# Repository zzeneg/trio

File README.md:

# trio

Modular unibody keyboard with two VIK modules.

> [!CAUTION]
> This keyboard is designed for minimal vertical spacing (19x16mm). Regular keycaps will not fit, you must print your own - for example my [DES MinY](https://github.com/zzeneg/PseudoMakeMeKeyCapProfiles?tab=readme-ov-file#update-from-zzeneg).
>
> It's created as a cheap prototype to test VIK abilities and modules - all PCBs are under 100x100mm, one-piece case <0.3kg for cheap JLCPCB shipping.
>
> Build process requires a lot of hand-soldering with 0.5mm pitch, you need good tools and experience to do that.
>
> I do not recommend to build it exactly like that, but to use it as inspiration for your projects. Feel free to use and improve KiCad and Fusion 360 source files.

## Features

- **MinY (19x16mm) spacing**
- 36 KS-33 (Gateron Low Profile) keys with hotswap
- central PCB with two independent VIKs, DRV2605L haptic feedback and rotary encoder
- periferal PCBs for keys
- 3D printed case with 1.28" display, Azoteq TPS65 touchpad and 33mm encoder

## Photos

## Gerber files

- [Main PCB](./pcb/production/main.zip)
- [Side PCB](./pcb/production/side.zip)
- Azoteq [VIK adapter](https://github.com/sadekbaroudi/vik/tree/master/pcb/azoteq-tps)
- Display [VIK adapter](https://github.com/zzeneg/vik-display-adapter) - 1.28" round version

## Case files

- [v0.1](./case/main-0.1.stl)
- [v0.2](./case/main-0.1.stl) - higher version, should work but untested

## Firmware

[Companion app](https://github.com/zzeneg/qmk-hid-host) for Raw HID communication. Use `"productId": 2120` for that keyboard.

#### QMK

Please see main `config.h` and `rules.mk` for comments and available options.

- [source code](https://github.com/zzeneg/qmk_firmware/tree/feature/zzeneg/keyboards/trio)
- [pre-compiled files](https://github.com/zzeneg/qmk_firmware/releases/tag/zzeneg)

#### Vial

- [source code](https://github.com/zzeneg/vial-qmk/tree/feature/zzeneg/keyboards/trio)
- [pre-compiled files](https://github.com/zzeneg/vial-qmk/releases/tag/zzeneg)

## Bill of materials

- [PCB](./pcb/production/pcb.zip)
- 36 KS-33 switches
- 36 hotswap sockets for KS-33 switches
- 3D printed case
- Azoteq TPS65 touchpad
- Azoteq [VIK adapter](https://github.com/sadekbaroudi/vik/tree/master/pcb/azoteq-tps)
- Bare 1.28" round [display](https://www.aliexpress.com/item/1005006051175539.html) - **without PCB**
- Display [VIK adapter](https://github.com/zzeneg/vik-display-adapter) - 1.28" round version **+ adapter's BOM**
- Helios-sized (26 GPIOs) [RP2040](https://www.aliexpress.com/item/1005006130019224.html) MCU
- 37 [SMD SOD-123 1N4148](https://www.aliexpress.com/item/1005002882901030.html) diodes
- [Vertical](https://www.aliexpress.com/item/10000000737049.html) and [horizontal](https://www.aliexpress.com/item/4000106123266.html) 12pin FFC/FPC connectors
- 12pin 0.5mm pitch 6cm [FFC cable](https://www.aliexpress.com/item/1005002468369055.html) - **both reverse and forward variants**
- short [EC11 rotary encoder](https://www.aliexpress.com/item/1005002109267228.html)
- 32mm [encoder knob](https://www.aliexpress.com/item/32749414806.html)
- SMD 4x4x1.5mm [push button](https://www.aliexpress.com/item/32802382507.html)
- 4mm [M2 screws with flat head](https://www.aliexpress.com/item/4001248931159.html)
- M2 [heatset inserts](https://www.aliexpress.com/item/1005004624377733.html) - 3mm length, 3.2mm diameter for resin case or 3.5mm for Nylon/PLA
- [7x1.5 legs](https://www.aliexpress.com/item/1005002995402961.html)
- for haptic feedback:
  - DRV2605L motor controller
  - 2 1uF capacitors (SMD 1206 size)
  - 2 4.7kOhm resistors (SMD 1206 size)
  - LRA or ERM [motor](https://docs.qmk.fm/#/feature_haptic_feedback?id=known-supported-hardware)

## Build notes

- side PCBs have two keys that have to be broken off and handwired to correct places (diodes stay on the big part)
- rotary encoder uses GPIO from VIK2, so Azoteq has to be connected to VIK2 port, and display to VIK1. Make sure to bridge solder jumpers on the back.
- cheap ERM motors may not have enough internal resistance, if you motor does not work, try to add 5-10R resistor to it
- see photos for FFC connections

## Development

For proper KiCad setup install my [zzkeeb](https://github.com/zzeneg/zzkeeb/blob/main/README.md#installation) library

## Support

If you like my work and want to support my future designs, please consider [sponsorship](https://github.com/sponsors/zzeneg).

#### Sponsors

Thank you very much for your support!

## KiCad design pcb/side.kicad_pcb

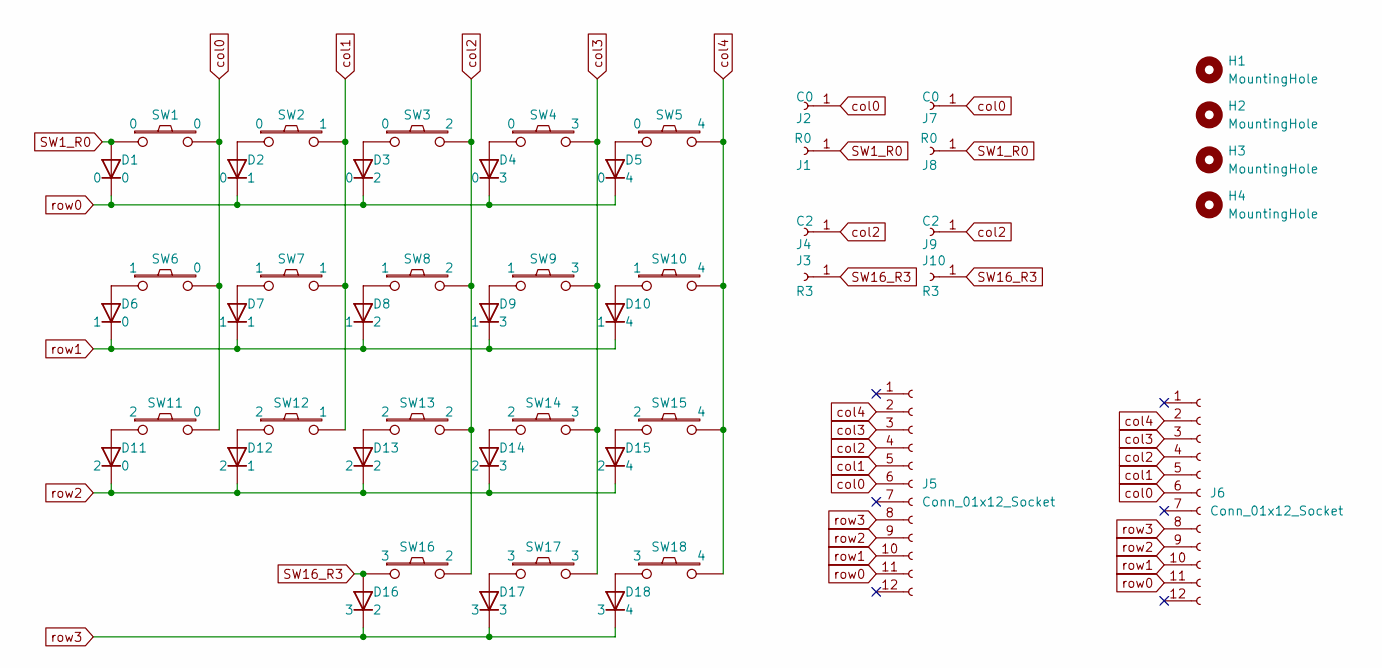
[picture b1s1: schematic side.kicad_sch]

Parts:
D1, D2, D3, D4, D5, D6, D7, D8, D9, D10, D11, D12, D13, D14, D15, D16, D17, D18: D; Diode_1N4148-SOD123-reversible-flip3d
H1, H2, H3, H4: MountingHole; Hole_M2
J1, J8: R0; TestPoint_THTPad_D1.5mm_Drill0.7mm
J2, J7: C0; TestPoint_THTPad_D1.5mm_Drill0.7mm
J3, J10: R3; TestPoint_THTPad_D1.5mm_Drill0.7mm
J4, J9: C2; TestPoint_THTPad_D1.5mm_Drill0.7mm
J5, J6: Conn_01x12_Socket; Connector_FFC-12pin-0.5mm-horizontal
SW1, SW2, SW3, SW4, SW5, SW6, SW7, SW8, SW9, SW10, SW11, SW12, SW13, SW14, SW15, SW16, SW17, SW18: Switch; Switch_KS-miny-reversible-hotswap-south

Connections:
unnamed: D2.2 (A), SW2.1
unnamed: D3.2 (A), SW3.1
unnamed: D4.2 (A), SW4.1
unnamed: D5.2 (A), SW5.1
unnamed: D6.2 (A), SW6.1
unnamed: D7.2 (A), SW7.1
unnamed: D8.2 (A), SW8.1
unnamed: D9.2 (A), SW9.1
unnamed: D10.2 (A), SW10.1
unnamed: D11.2 (A), SW11.1
unnamed: D12.2 (A), SW12.1
unnamed: D13.2 (A), SW13.1
unnamed: D14.2 (A), SW14.1
unnamed: D15.2 (A), SW15.1
unnamed: D17.2 (A), SW17.1
unnamed: D18.2 (A), SW18.1
SW1_R0: D1.2 (A), J1.1, J8.1, SW1.1
SW16_R3: D16.2 (A), J3.1, J10.1, SW16.1
col0: J2.1, J5.6, J6.6, J7.1, SW1.2, SW6.2, SW11.2
col1: J5.5, J6.5, SW2.2, SW7.2, SW12.2
col2: J4.1, J5.4, J6.4, J9.1, SW3.2, SW8.2, SW13.2, SW16.2
col3: J5.3, J6.3, SW4.2, SW9.2, SW14.2, SW17.2
col4: J5.2, J6.2, SW5.2, SW10.2, SW15.2, SW18.2
row0: D1.1 (K), D2.1 (K), D3.1 (K), D4.1 (K), D5.1 (K), J5.11, J6.11
row1: D6.1 (K), D7.1 (K), D8.1 (K), D9.1 (K), D10.1 (K), J5.10, J6.10
row2: D11.1 (K), D12.1 (K), D13.1 (K), D14.1 (K), D15.1 (K), J5.9, J6.9
row3: D16.1 (K), D17.1 (K), D18.1 (K), J5.8, J6.8

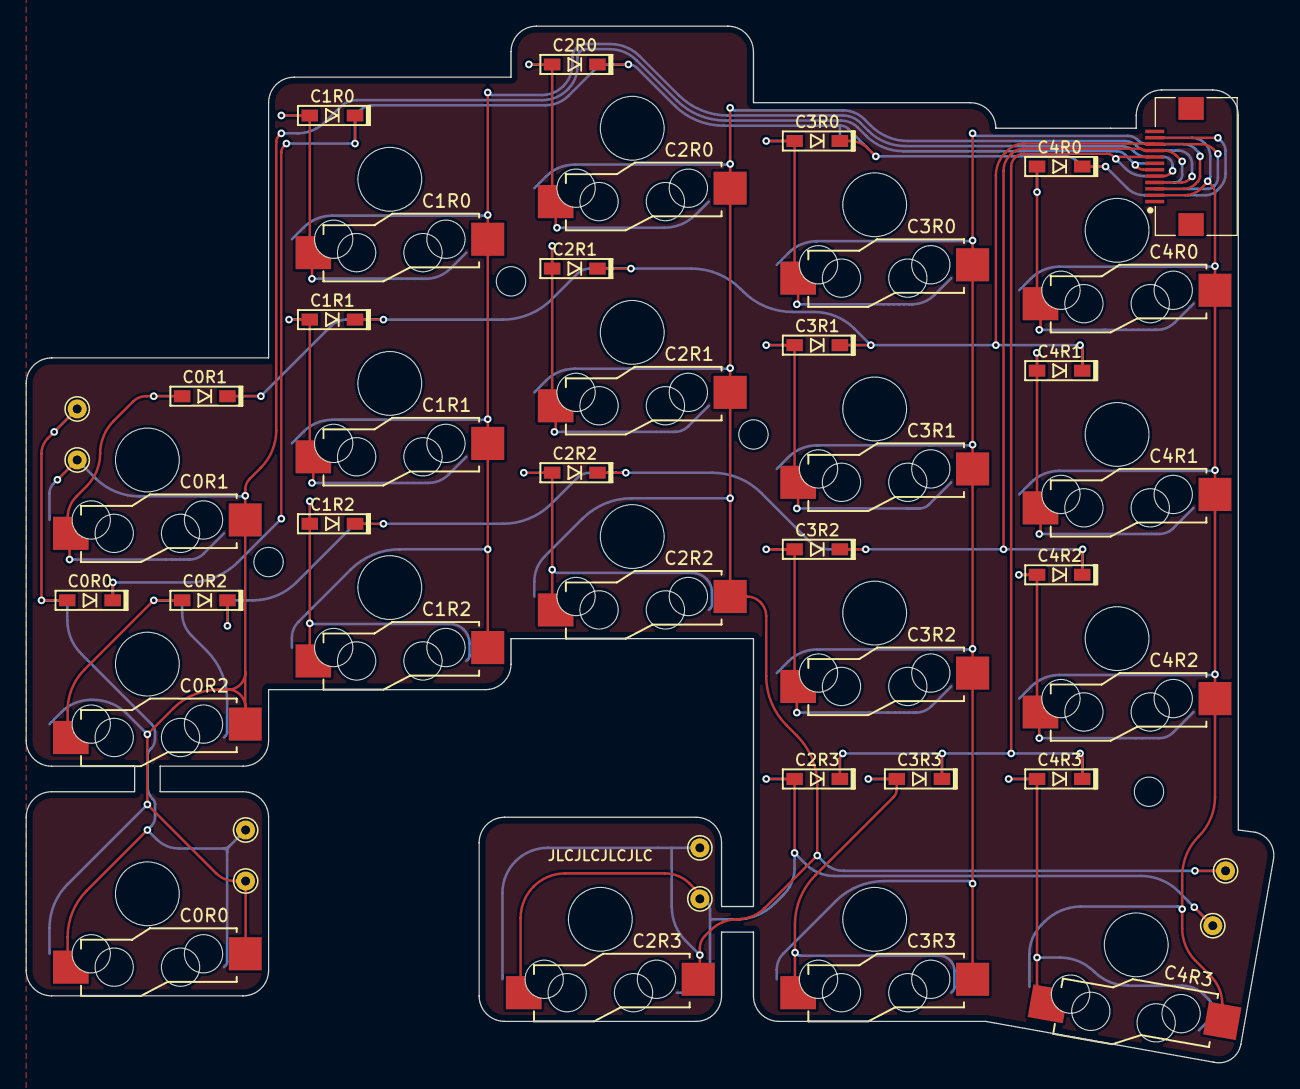
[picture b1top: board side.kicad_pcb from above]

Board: 2 copper layers, 97.8 x 81.2 mm, 50 parts (1 on the bottom side), 27 nets.

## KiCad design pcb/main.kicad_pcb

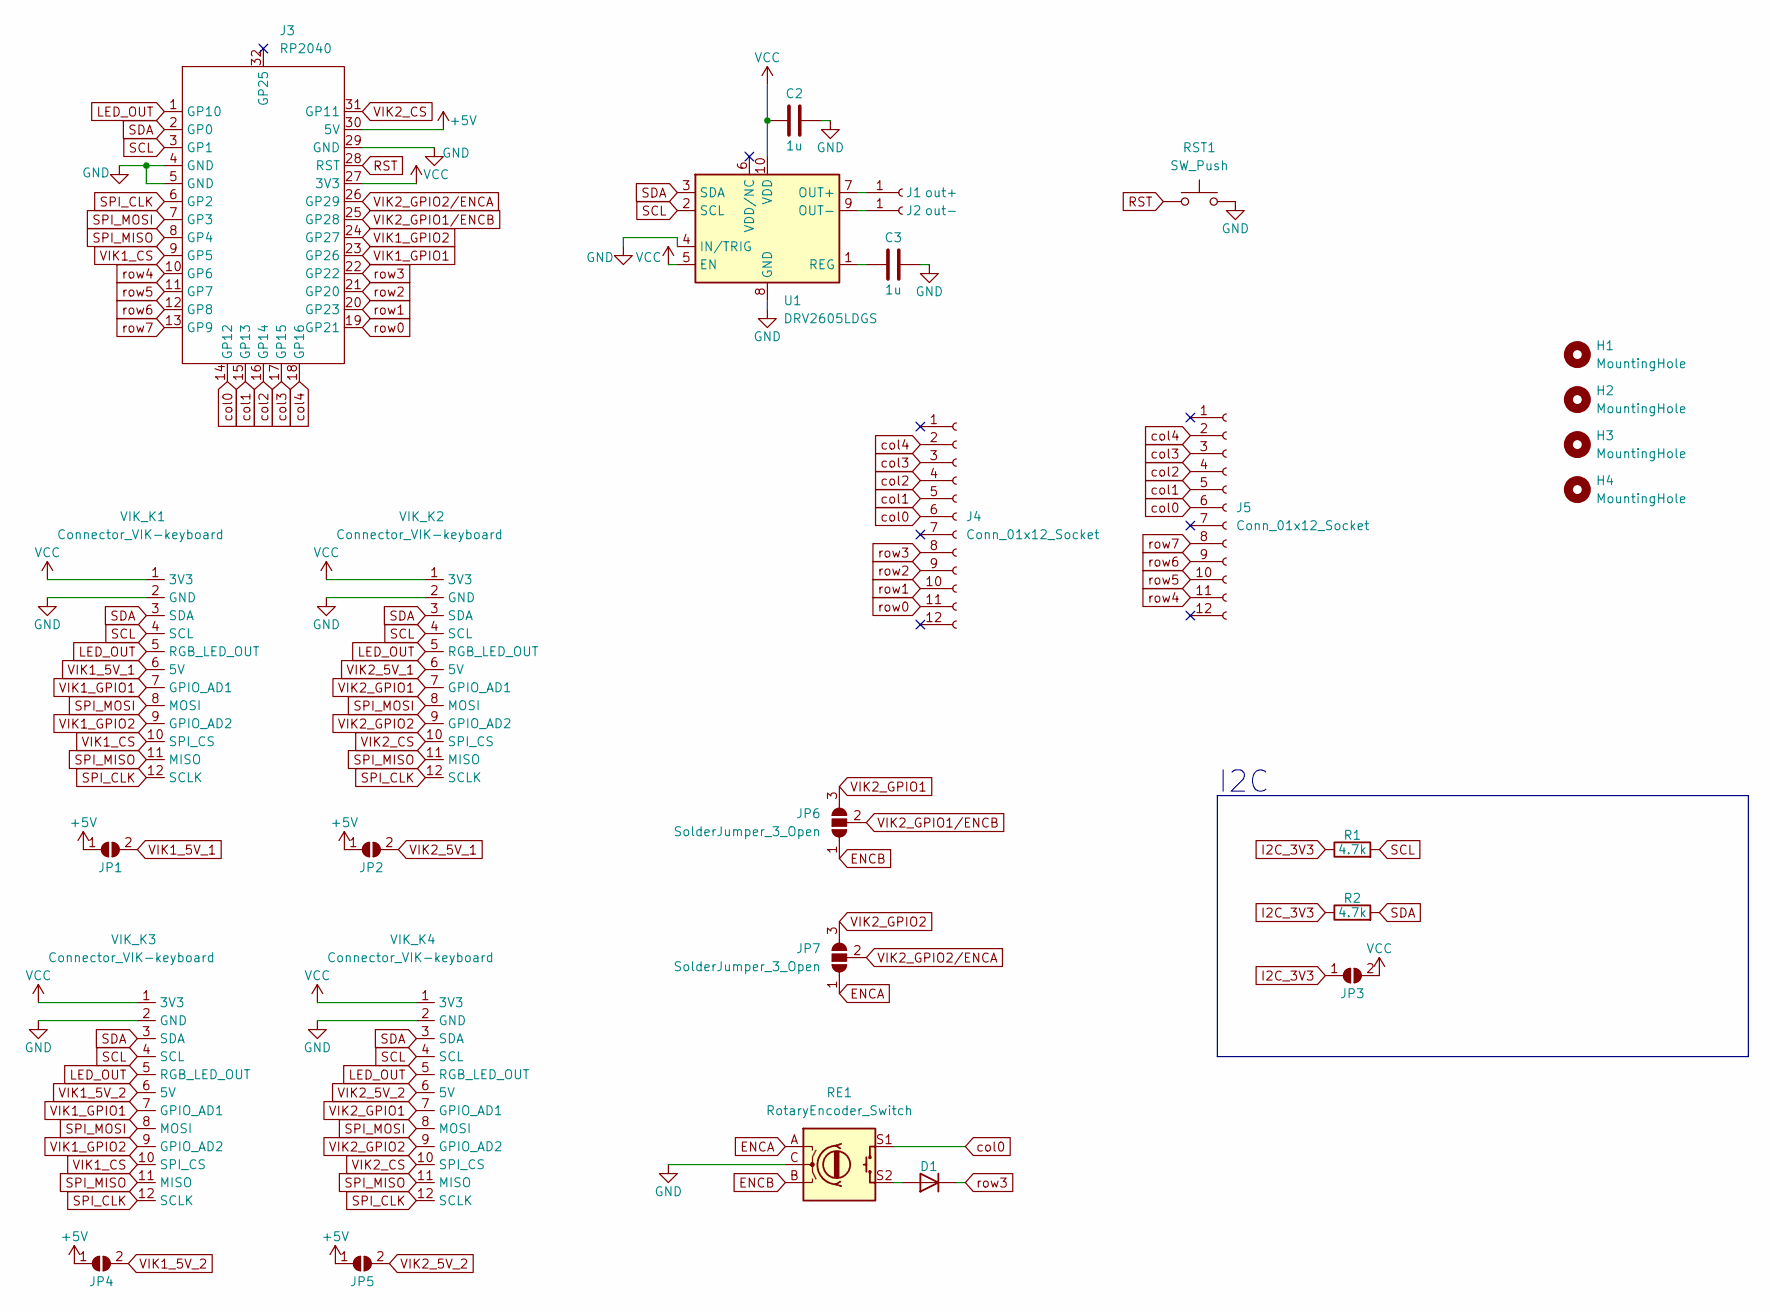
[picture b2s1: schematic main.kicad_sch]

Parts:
C2, C3: 1u; C_1206_3216Metric
D1: D; Diode_1N4148-SOD123
H1, H2, H3, H4: MountingHole; Hole_M2
J1: out+; TestPoint_THTPad_D2.0mm_Drill1.0mm
J2: out-; TestPoint_THTPad_D2.0mm_Drill1.0mm
J3: RP2040; MCU_rp2040-helios
J4, J5: Conn_01x12_Socket; Connector_FFC-12pin-0.5mm-horizontal
JP1, JP2, JP4, JP5: 5V; SolderJumper-2_P1.3mm_Open_RoundedPad1.0x1.5mm
JP3: VCC; SolderJumper-2_P1.3mm_Open_RoundedPad1.0x1.5mm
JP6, JP7: SolderJumper_3_Open; SolderJumper-3_P1.3mm_Open_Pad1.0x1.5mm
R1, R2: 4.7k; R_1206_3216Metric
RE1: RotaryEncoder_Switch; RotaryEncoder_EC11
RST1: SW_Push; Button_SW_SPST_SKQG_WithoutStem
U1: DRV2605LDGS; VSSOP-10_3x3mm_P0.5mm
VIK_K1, VIK_K2: Connector_VIK-keyboard; Connector_VIK-horizontal-keyboard
VIK_K3, VIK_K4: Connector_VIK-keyboard; Connector_VIK-vertical-keyboard

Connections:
+5V: J3.30 (5V), JP1.1 (A), JP2.1 (A), JP4.1 (A), JP5.1 (A)
ENCA: JP7.1 (A), RE1.A
ENCB: JP6.1 (A), RE1.B
GND: C2.2, C3.2, J3.4 (GND), J3.5 (GND), J3.29 (GND), RE1.C, RST1.2, U1.4 (IN/TRIG), U1.8 (GND), VIK_K1.2 (GND), VIK_K2.2 (GND), VIK_K3.2 (GND), VIK_K4.2 (GND)
I2C_3V3: JP3.1 (A), R1.1, R2.1
LED_OUT: J3.1 (GP10), VIK_K1.5 (RGB_LED_OUT), VIK_K2.5 (RGB_LED_OUT), VIK_K3.5 (RGB_LED_OUT), VIK_K4.5 (RGB_LED_OUT)
unnamed: D1.2 (A), RE1.S2
unnamed: J1.1, U1.7 (OUT+)
unnamed: J2.1, U1.9 (OUT-)
unnamed: C3.1, U1.1 (REG)
RST: J3.28 (RST), RST1.1
SCL: J3.3 (GP1), R1.2, U1.2 (SCL), VIK_K1.4 (SCL), VIK_K2.4 (SCL), VIK_K3.4 (SCL), VIK_K4.4 (SCL)
SDA: J3.2 (GP0), R2.2, U1.3 (SDA), VIK_K1.3 (SDA), VIK_K2.3 (SDA), VIK_K3.3 (SDA), VIK_K4.3 (SDA)
SPI_CLK: J3.6 (GP2), VIK_K1.12 (SCLK), VIK_K2.12 (SCLK), VIK_K3.12 (SCLK), VIK_K4.12 (SCLK)
SPI_MISO: J3.8 (GP4), VIK_K1.11 (MISO), VIK_K2.11 (MISO), VIK_K3.11 (MISO), VIK_K4.11 (MISO)
SPI_MOSI: J3.7 (GP3), VIK_K1.8 (MOSI), VIK_K2.8 (MOSI), VIK_K3.8 (MOSI), VIK_K4.8 (MOSI)
VCC: C2.1, J3.27 (3V3), JP3.2 (B), U1.5 (EN), U1.10 (VDD), VIK_K1.1 (3V3), VIK_K2.1 (3V3), VIK_K3.1 (3V3), VIK_K4.1 (3V3)
VIK1_5V_1: JP1.2 (B), VIK_K1.6 (5V)
VIK1_5V_2: JP4.2 (B), VIK_K3.6 (5V)
VIK1_CS: J3.9 (GP5), VIK_K1.10 (SPI_CS), VIK_K3.10 (SPI_CS)
VIK1_GPIO1: J3.23 (GP26), VIK_K1.7 (GPIO_AD1), VIK_K3.7 (GPIO_AD1)
VIK1_GPIO2: J3.24 (GP27), VIK_K1.9 (GPIO_AD2), VIK_K3.9 (GPIO_AD2)
VIK2_5V_1: JP2.2 (B), VIK_K2.6 (5V)
VIK2_5V_2: JP5.2 (B), VIK_K4.6 (5V)
VIK2_CS: J3.31 (GP11), VIK_K2.10 (SPI_CS), VIK_K4.10 (SPI_CS)
VIK2_GPIO1: JP6.3 (B), VIK_K2.7 (GPIO_AD1), VIK_K4.7 (GPIO_AD1)
VIK2_GPIO1/ENCB: J3.25 (GP28), JP6.2 (C)
VIK2_GPIO2: JP7.3 (B), VIK_K2.9 (GPIO_AD2), VIK_K4.9 (GPIO_AD2)
VIK2_GPIO2/ENCA: J3.26 (GP29), JP7.2 (C)
col0: J3.14 (GP12), J4.6, J5.6, RE1.S1
col1: J3.15 (GP13), J4.5, J5.5
col2: J3.16 (GP14), J4.4, J5.4
col3: J3.17 (GP15), J4.3, J5.3
col4: J3.18 (GP16), J4.2, J5.2
row0: J3.19 (GP21), J4.11
row1: J3.20 (GP23), J4.10
row2: J3.21 (GP20), J4.9
row3: D1.1 (K), J3.22 (GP22), J4.8
row4: J3.10 (GP6), J5.11
row5: J3.11 (GP7), J5.10
row6: J3.12 (GP8), J5.9
row7: J3.13 (GP9), J5.8

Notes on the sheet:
I2C

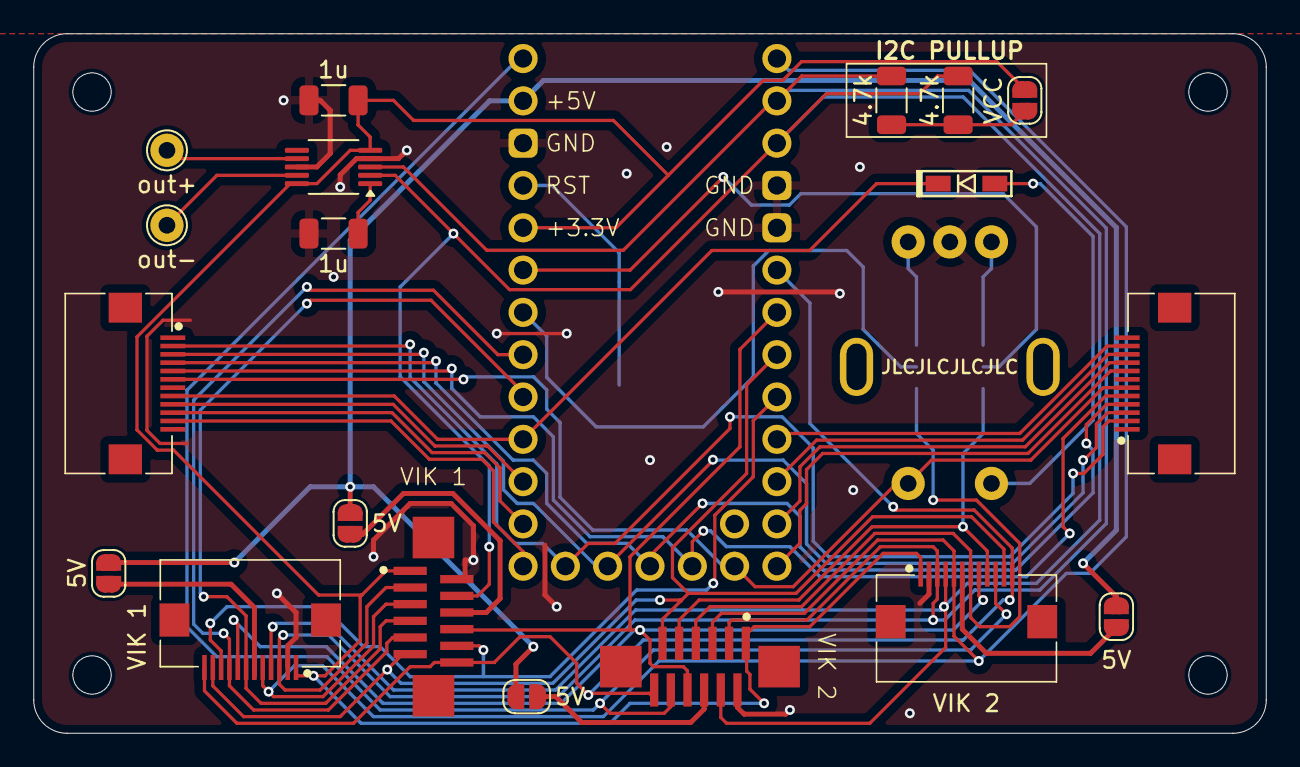
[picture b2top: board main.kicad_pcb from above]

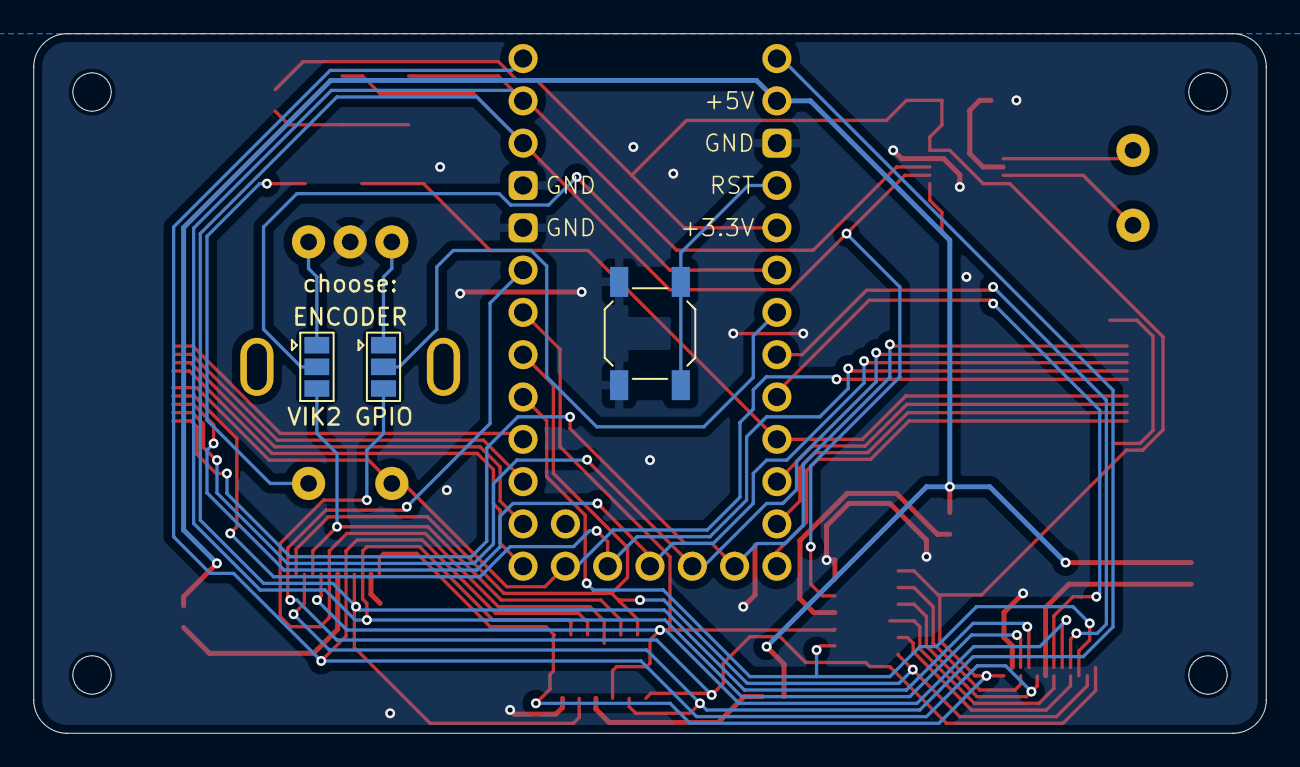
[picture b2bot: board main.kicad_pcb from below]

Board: 2 copper layers, 74.0 x 42.0 mm, 28 parts (4 on the bottom side), 42 nets.

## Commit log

2024-03-24 add side pcb
2024-03-24 add main pcb
2024-03-24 add case
2024-03-26 small updates
2024-04-14 fix case
2024-04-17 schematic draft
2024-04-17 jumpers for VIK GPIO, small side updates
2024-04-19 update case
2024-04-21 add readme
2024-04-22 add funding
2024-04-27 fix links to firmware
